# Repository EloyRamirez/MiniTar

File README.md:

# MiniTar
Personal project to create smallest guitar hero controller.

I'm building a guitar hero (clone hero) controller with the bare minimum functions (frets and strum bar) and I'm trying to make it as small and compact as I can.
I'm using an RP2040 and followed the minimal hardware design doc from RasPi as reference. 
It's my first time designing a board just using components and no breakouts. 

Using JLCPCB for manufacturing and assembly of SMT components. DFM checks tailored to their requirements.
Soldering THT components myself.

Using the Santroller Configurator to program RP2040 firmware.

My reference for size is the Nintendo DS version of Guitar Hero which came with a controller attachment specifically for the Nintendo DS Lite that connects into the GBA port on the bottom to use the fret buttons. My goal being that the final product is less in volume than a Nintendo DS Lite 211,603mm^3.

The case was modeled in Fusion 360 with a final volume of 38,031mm^3.
Using JLC3DP for 3D printing.

Future plans: Add gyro and wammy bar.

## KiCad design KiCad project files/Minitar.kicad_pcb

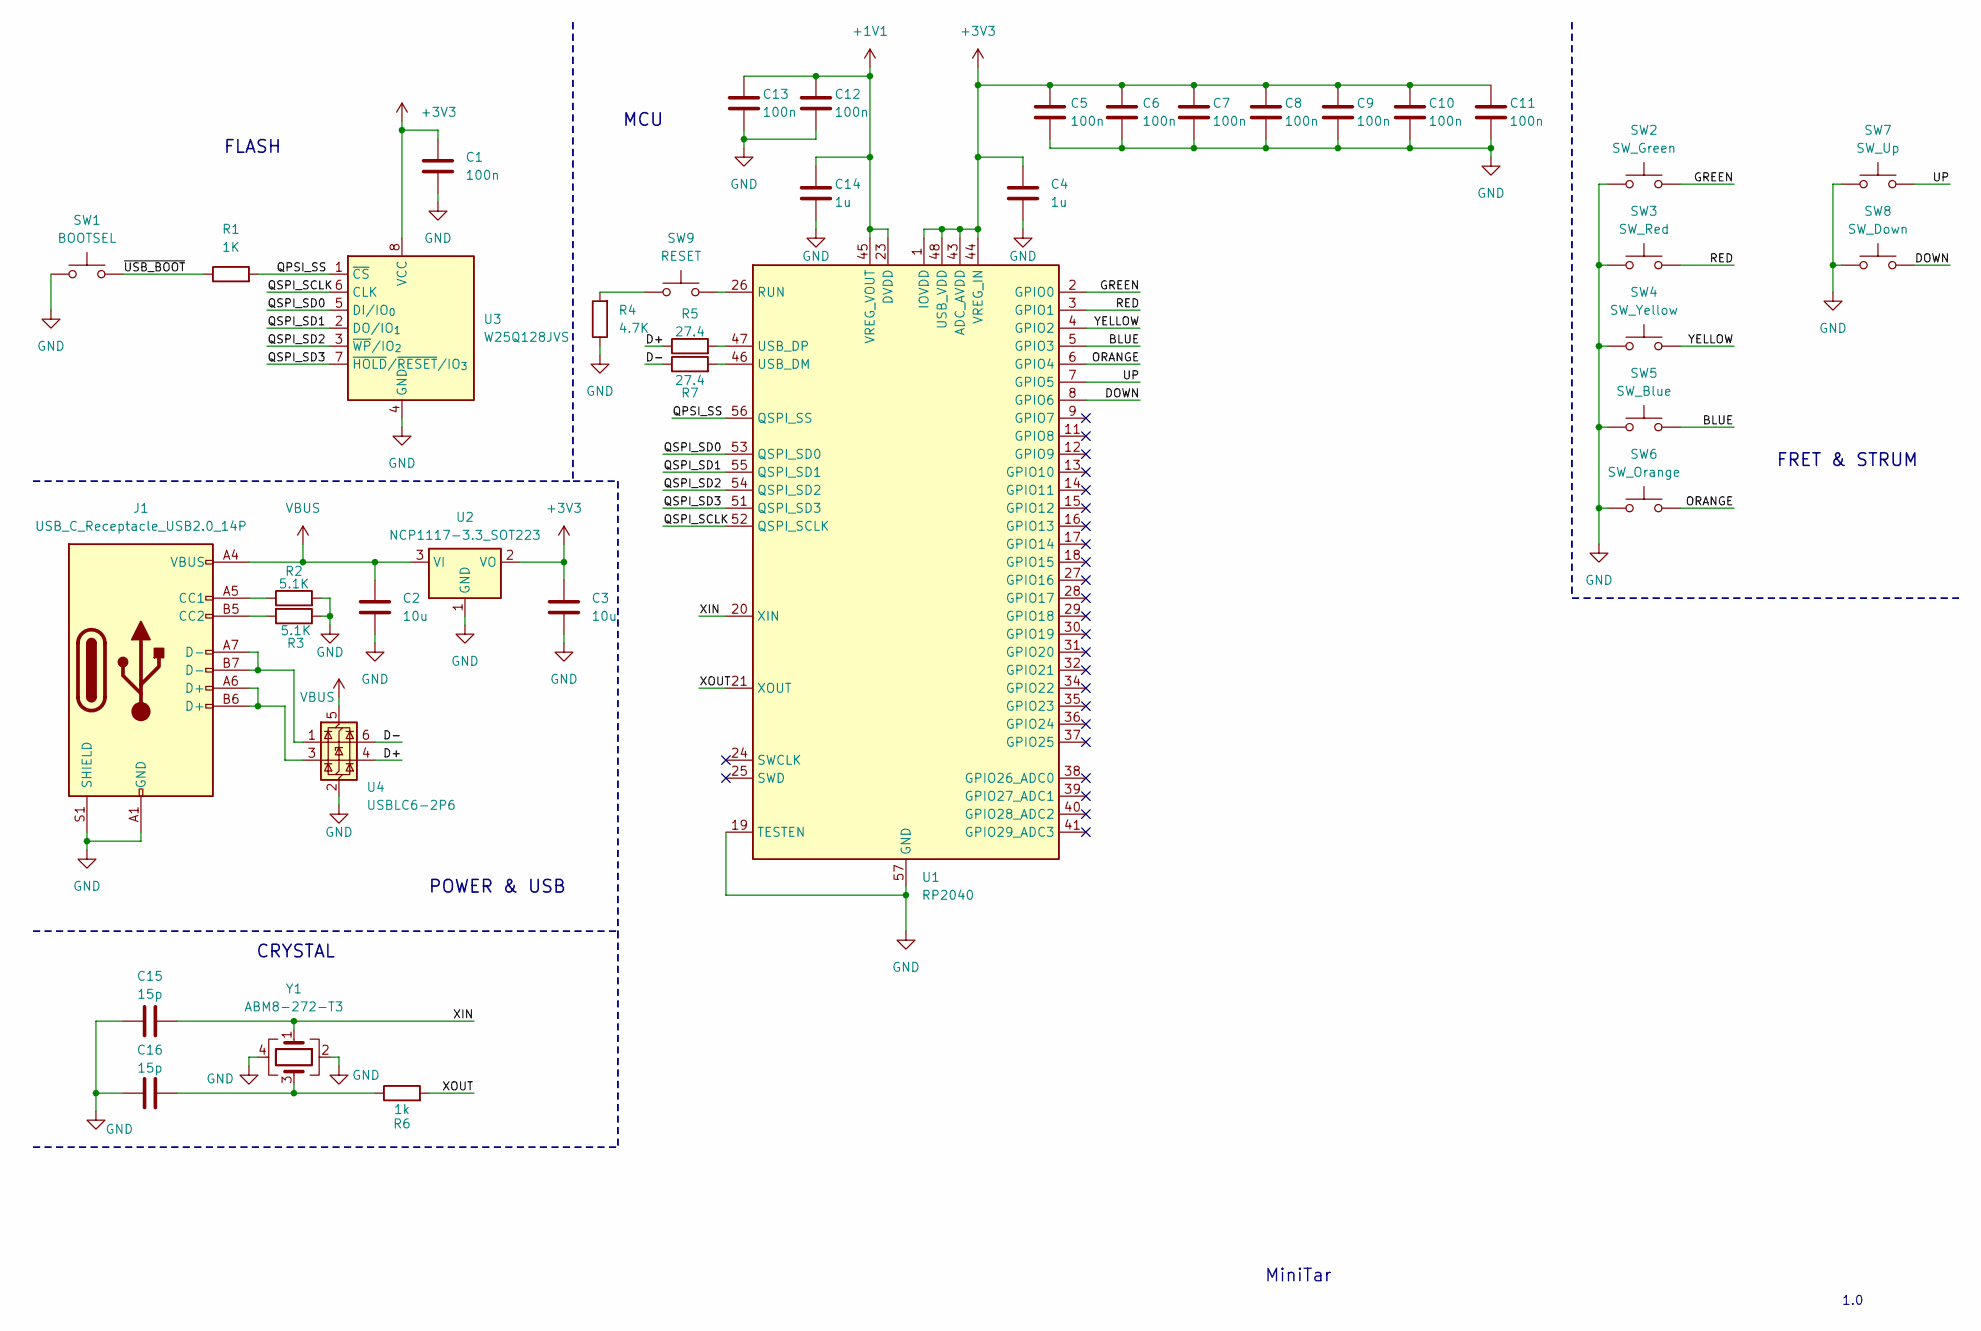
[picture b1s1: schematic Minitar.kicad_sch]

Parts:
C1, C5, C6, C7, C8, C9, C10, C11, C12, C13: 100n; C_0402_1005Metric
C2, C3: 10u; C_0805_2012Metric
C4, C14: 1u; C_0402_1005Metric
C15, C16: 15p; C_0402_1005Metric
J1: USB_C_Receptacle_USB2.0_14P; USB_C_Receptacle_G-Switch_GT-USB-7010ASV
R1: 1K; R_0402_1005Metric
R2, R3: 5.1K; R_0402_1005Metric
R4: 4.7K; R_0402_1005Metric
R5, R7: 27.4; R_0402_1005Metric
R6: 1k; R_0402_1005Metric
SW1: BOOTSEL; SW_Tactile_SPST_NO_Straight_CK_PTS636Sx25SMTRLFS
SW2: SW_Green; SW_Kailh_Choc_V1
SW3: SW_Red; SW_Kailh_Choc_V1
SW4: SW_Yellow; SW_Kailh_Choc_V1
SW5: SW_Blue; SW_Kailh_Choc_V1
SW6: SW_Orange; SW_Kailh_Choc_V1
SW7: SW_Up; SW_Kailh_KH
SW8: SW_Down; SW_Kailh_KH
SW9: RESET; SW_Tactile_SPST_NO_Straight_CK_PTS636Sx25SMTRLFS
U1: RP2040; QFN-56-1EP_7x7mm_P0.4mm_EP3.2x3.2mm
U2: NCP1117-3.3_SOT223; SOT-223-3_TabPin2
U3: W25Q128JVS; SOIC-8_5.3x5.3mm_P1.27mm
U4: USBLC6-2P6; SOT-666
Y1: ABM8-272-T3; Crystal_SMD_Abracon_ABM8G-4Pin_3.2x2.5mm

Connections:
+1V1: C12.1, C13.1, C14.1, U1.23 (DVDD), U1.45 (VREG_VOUT), U1.50 (DVDD)
+3V3: C1.1, C3.1, C4.1, C5.1, C6.1, C7.1, C8.1, C9.1, C10.1, C11.1, U1.1 (IOVDD), U1.10 (IOVDD), U1.22 (IOVDD), U1.33 (IOVDD), U1.42 (IOVDD), U1.43 (ADC_AVDD), U1.44 (VREG_IN), U1.48 (USB_VDD), U1.49 (IOVDD), U2.2 (VO), U3.8 (VCC)
/BLUE: SW5.2, U1.5 (GPIO3)
/D+: R5.1, U4.4 (I/O2)
/D-: R7.1, U4.6 (I/O1)
/DOWN: SW8.2, U1.8 (GPIO6)
/GREEN: SW2.2, U1.2 (GPIO0)
/ORANGE: SW6.2, U1.6 (GPIO4)
/QPSI_SS: R1.2, U1.56 (QSPI_SS), U3.1 (~CS)
/QSPI_SCLK: U1.52 (QSPI_SCLK), U3.6 (CLK)
/QSPI_SD0: U1.53 (QSPI_SD0), U3.5 (DI/IO_{0})
/QSPI_SD1: U1.55 (QSPI_SD1), U3.2 (DO/IO_{1})
/QSPI_SD2: U1.54 (QSPI_SD2), U3.3 (~WP/IO_{2})
/QSPI_SD3: U1.51 (QSPI_SD3), U3.7 (~HOLD/~RESET/IO_{3})
/RED: SW3.2, U1.3 (GPIO1)
/UP: SW7.2, U1.7 (GPIO5)
/XIN: C15.2, U1.20 (XIN), Y1.1
/XOUT: R6.2, U1.21 (XOUT)
/YELLOW: SW4.2, U1.4 (GPIO2)
/~USB_BOOT: R1.1, SW1.2
GND: C1.2, C2.2, C3.2, C4.2, C5.2, C6.2, C7.2, C8.2, C9.2, C10.2, C11.2, C12.2, C13.2, C14.2, C15.1, C16.1, J1.A1 (GND), J1.A12 (GND), J1.B1 (GND), J1.B12 (GND), J1.S1 (SHIELD), R2.2, R3.1, R4.1, SW1.1, SW2.1, SW3.1, SW4.1, SW5.1, SW6.1, SW7.1, SW8.1, U1.19 (TESTEN), U1.57 (GND), U2.1 (GND), U3.4 (GND), U4.2 (GND), Y1.2, Y1.4
unnamed: C16.2, R6.1, Y1.3
unnamed: J1.A5 (CC1), R2.1
unnamed: J1.B5 (CC2), R3.2
unnamed: J1.A6 (D+), J1.B6 (D+), U4.3 (I/O2)
unnamed: J1.A7 (D-), J1.B7 (D-), U4.1 (I/O1)
unnamed: R4.2, SW9.1
unnamed: SW9.2, U1.26 (RUN)
unnamed: R7.2, U1.46 (USB_DM)
unnamed: R5.2, U1.47 (USB_DP)
VBUS: C2.1, J1.A4 (VBUS), J1.A9 (VBUS), J1.B4 (VBUS), J1.B9 (VBUS), U2.3 (VI), U4.5 (VBUS)

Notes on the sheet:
FRET & STRUM
MiniTar
1.0
POWER & USB
FLASH
CRYSTAL
MCU

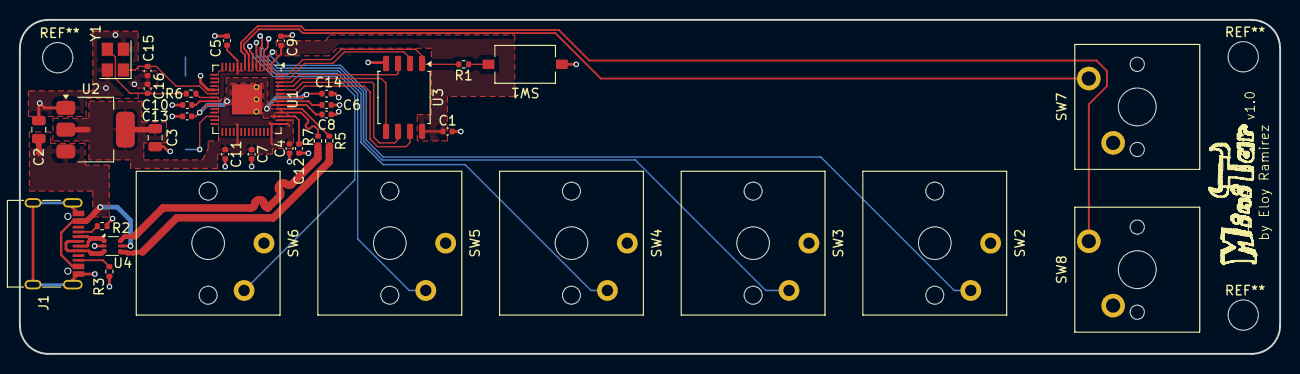
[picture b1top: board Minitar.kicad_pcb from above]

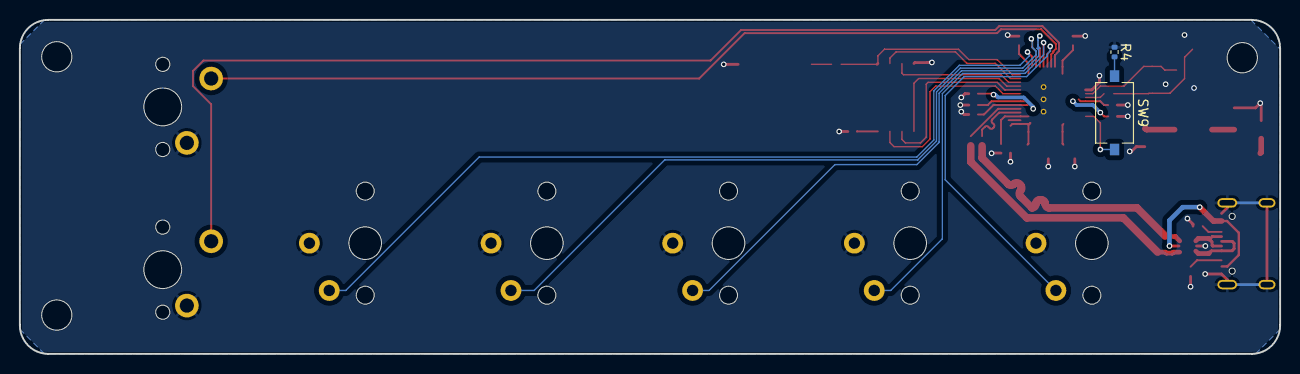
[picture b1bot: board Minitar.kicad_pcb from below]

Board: 2 copper layers, 133.2 x 35.3 mm, 38 parts (2 on the bottom side), 31 nets.

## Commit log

2025-03-25 Update README.md
    Updated project description
2025-03-25 Added KiCad project files
2025-03-25 Added screenshots of projects files
2025-04-03 Update README.md
    Added information on case and 3D printing
